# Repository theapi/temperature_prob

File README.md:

# Temperature Probe
A simple temperature probe using a thermistor &amp; a 4 digit 7 segment display

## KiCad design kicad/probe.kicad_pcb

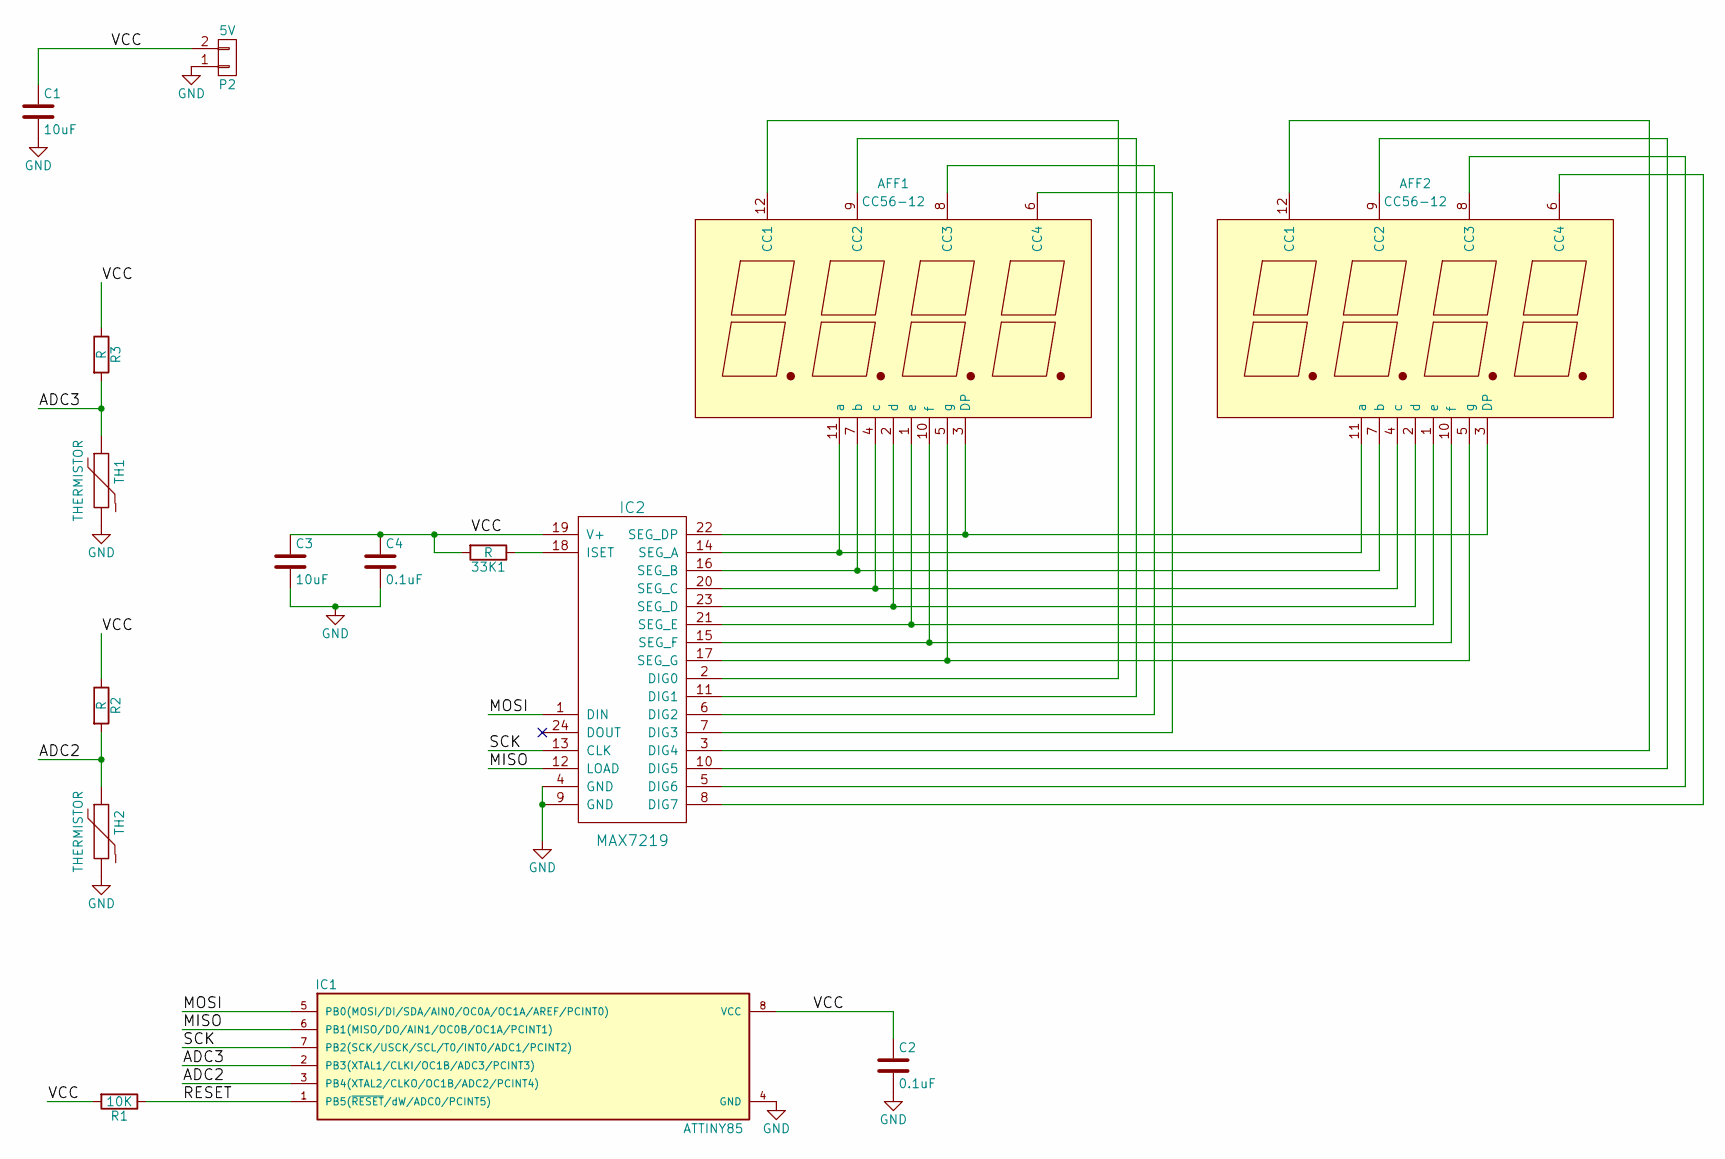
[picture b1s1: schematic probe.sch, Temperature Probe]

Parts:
33K1: R; R_0805_HandSoldering
AFF1, AFF2: CC56-12; 4x7seg_CA
C1, C3: 10uF; C_0805_HandSoldering
C2, C4: 0.1uF; C_0805_HandSoldering
IC1: ATTINY85; DIP-8_W7.62mm
IC2: MAX7219; DIP-24_W7.62mm
P2: 5V; Pin_Header_Straight_1x02
R1: 10K; R_0805_HandSoldering
R2, R3: R; R_0805_HandSoldering
TH1, TH2: THERMISTOR; R1

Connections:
/ADC2: IC1.3 (PB4(XTAL2/CLKO/OC1B/ADC2/PCINT4)), R2.2, TH2.1
/ADC3: IC1.2 (PB3(XTAL1/CLKI/OC1B/ADC3/PCINT3)), R3.2, TH1.1
/MISO: IC1.6 (PB1(MISO/DO/AIN1/OC0B/OC1A/PCINT1)), IC2.12 (LOAD)
/MOSI: IC1.5 (PB0(MOSI/DI/SDA/AIN0/OC0A/OC1A/AREF/PCI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), IC2.1 (DIN)
/RESET: IC1.1 (PB5(~RESET~/dW/ADC0/PCINT5)), R1.1
/SCK: IC1.7 (PB2(SCK/USCK/SCL/T0/INT0/ADC1/PCINT2)), IC2.13 (CLK)
/VCC: 33K1.2, C1.1, C2.1, C3.1, C4.1, IC1.8 (VCC), IC2.19 (V+), P2.2, R1.2, R2.1, R3.1
GND: C1.2, C2.2, C3.2, C4.2, IC1.4 (GND), IC2.4 (GND), IC2.9 (GND), P2.1, TH1.2, TH2.2
unnamed: 33K1.1, IC2.18 (ISET)
unnamed: AFF1.1 (e), AFF2.1 (e), IC2.21 (SEG_E)
unnamed: AFF1.2 (d), AFF2.2 (d), IC2.23 (SEG_D)
unnamed: AFF1.3 (DP), AFF2.3 (DP), IC2.22 (SEG_DP)
unnamed: AFF1.4 (c), AFF2.4 (c), IC2.20 (SEG_C)
unnamed: AFF1.5 (g), AFF2.5 (g), IC2.17 (SEG_G)
unnamed: AFF1.6 (CC4), IC2.7 (DIG3)
unnamed: AFF1.7 (b), AFF2.7 (b), IC2.16 (SEG_B)
unnamed: AFF1.8 (CC3), IC2.6 (DIG2)
unnamed: AFF1.9 (CC2), IC2.11 (DIG1)
unnamed: AFF1.10 (f), AFF2.10 (f), IC2.15 (SEG_F)
unnamed: AFF1.11 (a), AFF2.11 (a), IC2.14 (SEG_A)
unnamed: AFF1.12 (CC1), IC2.2 (DIG0)
unnamed: AFF2.6 (CC4), IC2.8 (DIG7)
unnamed: AFF2.8 (CC3), IC2.5 (DIG6)
unnamed: AFF2.9 (CC2), IC2.10 (DIG5)
unnamed: AFF2.12 (CC1), IC2.3 (DIG4)

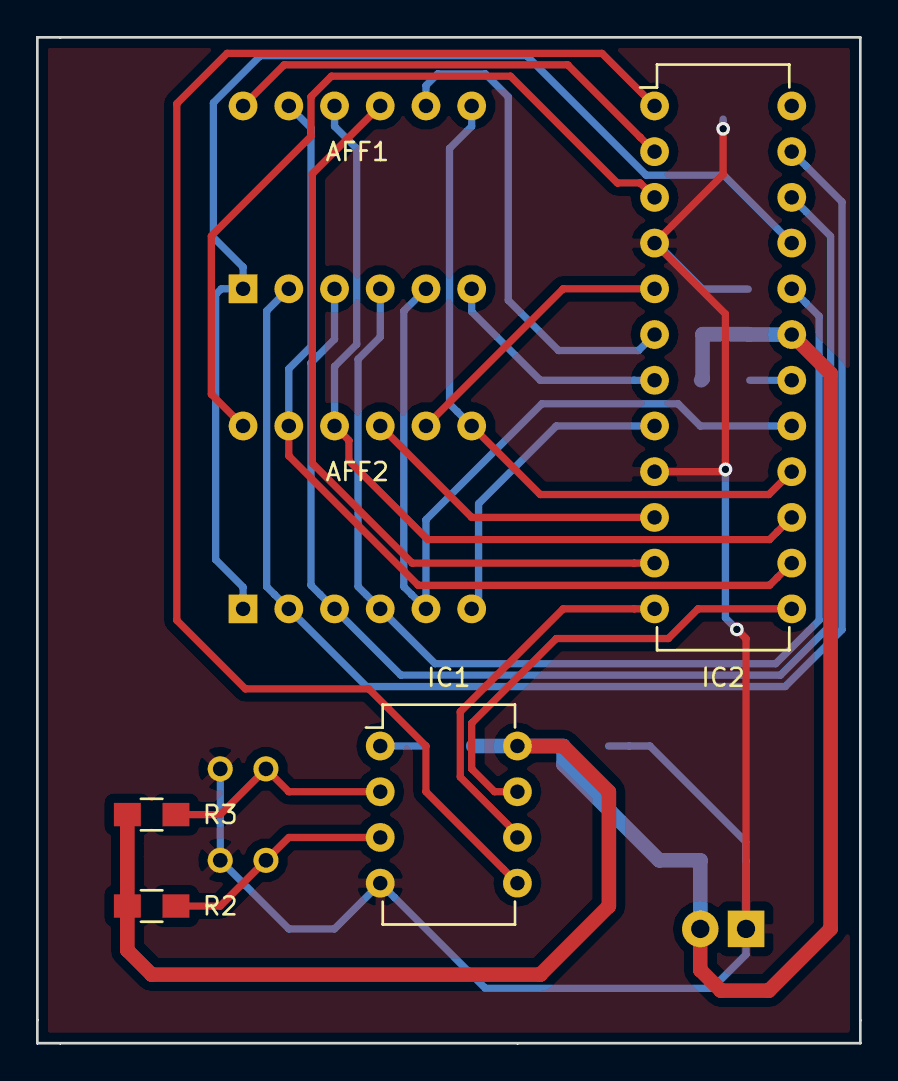
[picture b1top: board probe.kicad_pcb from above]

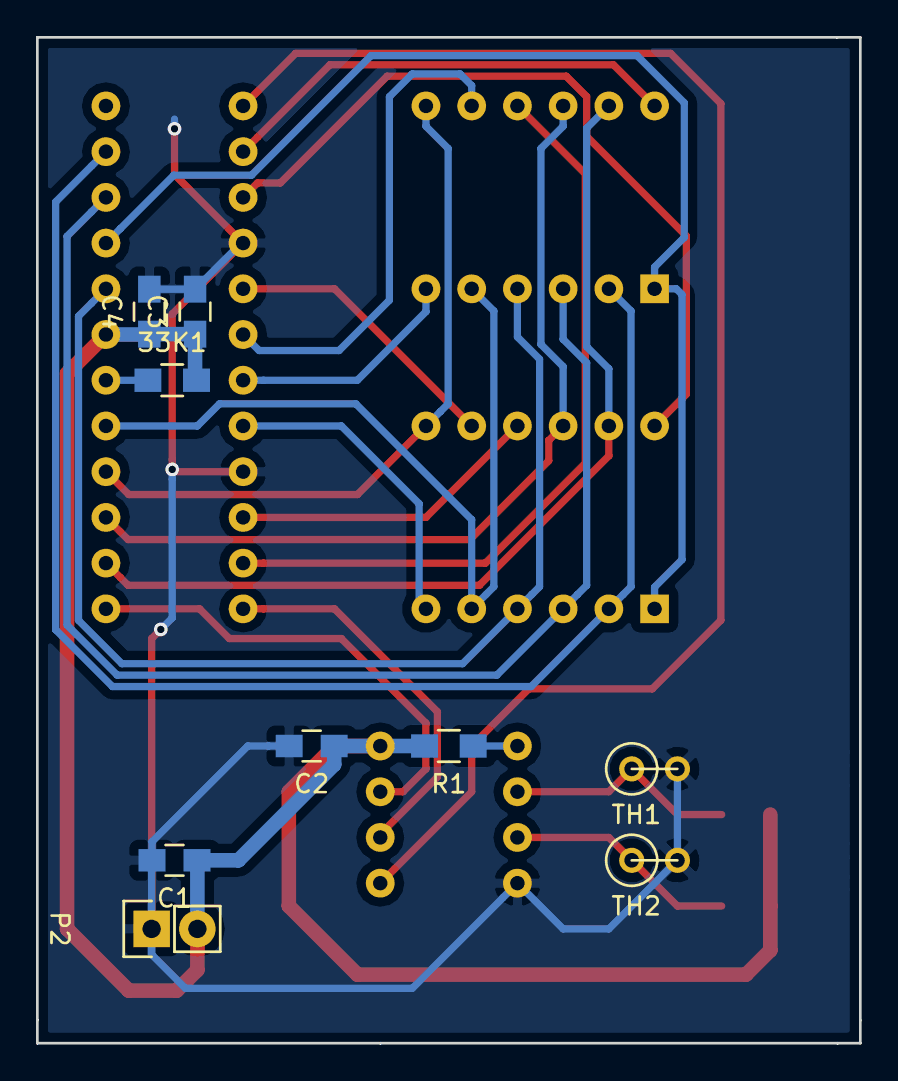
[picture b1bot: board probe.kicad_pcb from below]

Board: 2 copper layers, 45.7 x 55.9 mm, 15 parts (9 on the bottom side), 25 nets.

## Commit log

2016-09-12 Start of the schematic
2016-09-13 Schematic v0.1
2016-09-15 Docs
2016-09-15 Initial layout
2016-09-15 Drawing of the real display dimensions
2016-09-15 Blank Arduino sketch
2016-09-15 New layout with correct size display
2016-09-18 2 displays & 2 thermistors on perfboard
2016-09-18 Schematic pdf
2016-09-18 Initial routing
2016-09-18 Pin definitions
2016-09-18 Arduino Uno pin definitions too
2016-09-18 Layout tweek
2016-09-21 Initial max7219 communication
2016-09-21 Start of library
2016-09-22 Use Code B font
2016-09-24 Display the temperature
2016-09-28 Better accuracy
2016-09-28 Junk the first reading
2016-09-28 Readability
2016-10-02 Moved the digits one column to the right
